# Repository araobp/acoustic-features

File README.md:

# Acoustic features for low-end edge AI

**=> [Acoustic feature gallery (2D images)](./GALLERY.md)**

## Demo video on YouTube

Acoustic features acquired by my Acoustic Feature Camera:
- [video](https://youtu.be/UvSJ3fOOCXc)

Inference using X-CUBE-AI on STM32L476RG:
- [video](https://www.youtube.com/watch?v=wbkjt2Bl5TY)

Inference using Keras/TensorFlow on PC instead of X-CUBE-AI on STM32L476RG:
- [video 1](https://youtu.be/RV7oED41P2w)
- [video 2](https://youtu.be/4BaBL-gmQBk)

## Review on this project

I have discoverd that **low-end edge AI works very well** as long as the conditions described in this README are satisfied. If simple classification is a requirment, think of low-cost AI based on MCU before MPU/FPGA/GPU!

 I find the "life log" use case (dataset: "my home") in this project works very well, but the problem is that it takes a lot of efforts -- three hours for acquiring dataset at each room in my house. This is my hobboy project, and I do not need to worry about if this can make a profit or not.
 
"key word detection" use case is also not so bad. It can be used as voice commands to controll home applicances, such as "turn on!" or "turn off!".

"acoustic scene classification" is the hardest due to the disturbance from surrounding noises. I think it is not useful in a real world.

## Use cases in this project

- life log
- always-on key word detection (e.g., "OK Google" or "Alexa!")
- musical instrument classification
- acoustic scene classification

I have tested all of the use cases above, and confirmed that my device works well.

**Note: the size of neural network is so small that it is not a general purpose tool -- it is good at very limited number of classes.**

## Architecture

```
                                                         ARM Cortex-M4(STM32L476RG)
                                         ***** pre-processing *****           ***** inference *****
                                      ................................................................
                                      :   Filters for feature extraction        Inference on CNN     :
                                      :                                         ..................   :
Sound/voice ))) [MEMS mic]--PDM-->[DFSDM]--+->[]->[]->[]->[]---+----Features--->: code generated :   :
                                      :    |                   |                : by X-CUBE-AI   :   :
                                      :    +------------+      |                ..................   :
                                      :     +-----------|------+                                     :
                                      :     |           |                                            :
                                      :     V           V                                            :
                                      :..[USART]......[DAC]..........................................:
                                            |           |
                                            |           | *** monitoring raw sound ***
                                            |           +---> [Analog filter] --> head phone
                                       (features)
                                            |
                                            | *** learning ***
                                            +--(dataset)--> [oscilloscope.py/Win10 or RasPi3] Keras/TensorFlow
                                            |
                                            | *** inference ***
                                            +--(dataset)--> [oscilloscope.py/Win10 or RasPi3] Keras/TensorFlow
```

Platform:
- [Platform and tool chain](./PLATFORM.md)

## System components

I developed the following components:

- ["Acoustic feature camera" for deep learning (CubeMX/TrueSTUDIO)](./stm32/acoustic_feature_camera)
- [Arduino shield of one MEMS microphone with BLE module (KiCAD)](./kicad)
- [Oscilloscope GUI implementation on matplotlib/Tkinter (Python)](./oscilloscope)
- [Logger GUI (HTML5)](./html5)

## Deep learning on Keras/TensorFlow

I acquired data on my own by using the components above, and it took a lot of time and effort.

- [Dataset of each use case](./dataset)
- [Executing deep learning on Jupyter Notebook](./keras)
- [Dataset format](./FORMAT.md)

### Modeling a neural network

To run a neural network on MCU (STM32 in this project), it is necessary to make the network small enough to fit it into the RAM and the flash memory:
- Adopt a CNN model that is relatively smaller than other network models.
- Perform pre-processing based on signal processing to extract features for CNN.

Usually, raw sound data (PCM) is transformed into the following "coefficients" as features:
- MFSCs (Mel Frequency Spectral Coefficients): the technique is to mimic the human auditory system.
- MFCCs (Mel Frequency Cepstral Coefficients): the technique is similar to JPEG/MPEG's data compression.

**My experiments so far showed that MFSCs+CNN ourperformed MFCCs+DNN or MFCCs+CNN.** And DNN tends to use more memory space than CNN does (more flash memory space, in case of X-CUBE-AI). So I use MFSCs for deep learning in this project.

### CNN size

The following CNN model performs very well and avoids over-fittting in most of the use cases I have ever tried:

```
Orignal data size: PCM 16bit 512*32 (26.3msec*32)

SFFT/Spectrogram size
- Stride: 13.2msec * 64
- Ovelap: 50%

MFSCs resolution: filterbank of 40 triagle filters
Quantized input tensor: MFSCs int8_t (64, 40, 1)

However, X-CUBE-AI currently supports float32_t only, so int8_t is just for transmitting the data to PC over UART.

CNN model on Keras
_________________________________________________________________
Layer (type)                 Output Shape              Param #   
=================================================================
conv2d_81 (Conv2D)           (None, 62, 38, 8)         80        
_________________________________________________________________
max_pooling2d_79 (MaxPooling (None, 31, 19, 8)         0         
_________________________________________________________________
dropout_57 (Dropout)         (None, 31, 19, 8)         0         
_________________________________________________________________
conv2d_82 (Conv2D)           (None, 29, 17, 16)        1168      
_________________________________________________________________
max_pooling2d_80 (MaxPooling (None, 14, 8, 16)         0         
_________________________________________________________________
dropout_58 (Dropout)         (None, 14, 8, 16)         0         
_________________________________________________________________
conv2d_83 (Conv2D)           (None, 12, 6, 32)         4640      
_________________________________________________________________
max_pooling2d_81 (MaxPooling (None, 6, 3, 32)          0         
_________________________________________________________________
dropout_59 (Dropout)         (None, 6, 3, 32)          0         
_________________________________________________________________
flatten_27 (Flatten)         (None, 576)               0         
_________________________________________________________________
dense_62 (Dense)             (None, 128)               73856     
_________________________________________________________________
dropout_60 (Dropout)         (None, 128)               0         
_________________________________________________________________
dense_63 (Dense)             (None, 18)                2322      
=================================================================
Total params: 82,066
Trainable params: 82,066
Non-trainable params: 0
```

### Visualization of convolution layers

**=> [Japanese word "sushi" via convolution layer](./keras/Visualization_sushi.ipynb)**

### Memory consumption and inference performance

I loaded a trained CNN model (Keras model) into Cube.AI and generated code for inference. The model consumed only 25KBytes of SRAM and 105Kbytes (compressed) of Flash memory, and the duration of inference was around 170msec on STM32L476RG.

The duration of 170msec is acceptible (not too slow) in my use cases.

And I know that Arm is working on [Helium](https://www.arm.com/why-arm/technologies/helium), so it will be able to process acoustic features for inference in real time.

## Noise problems

```
         Room impulse response
                   :
                   V
Sound -->(Line distortion)--(+)->[Feature engineering]--Feature->[Normalization]->[Neural Network]->Inference
              convolved      ^
                             | Added
                             |
                      (Ambient noise)
```

### Effect of room impulse response on inference

I have been observing that **room impulse response** (it turns into **line distortion**) has an lot of effect on inference.

My strategy for tackling the problem is:
- use **the same device** for both acquiring features and inference on the device.
- use the device **at the same location** for both acquiring features and inference.
- never change the values of parameters for feature engineering (e.g., parameters for filters).

If the above conditions are satisfied, this small neural network works very well.

### Effect of ambient noise on inference

I have been observing that sound of air conditioner affects accuracy of inference significantly.

## References

- ["New Architectures Bringing AI to the Edge"](https://www.eetimes.com/document.asp?doc_id=1333920).
- [VGGish](https://github.com/tensorflow/models/tree/master/research/audioset)
- [Speech Processing for Machine Learning: Filter banks, Mel-Frequency Cepstral Coefficients (MFCCs) and What's In-Between](https://haythamfayek.com/2016/04/21/speech-processing-for-machine-learning.html)
- [STM32 Cube.AI](https://www.st.com/content/st_com/en/stm32-ann.html)

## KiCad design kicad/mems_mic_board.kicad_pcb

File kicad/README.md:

# Arduino shield of one MEMS microphone with RN4020

## Arduino shield

==> **[Schematic](./mems_mic_board.pdf)**

Note: the yellow jumper cable is for the MEMS mic to receive clock signal from DFSDM.

## Wireless transport

I follow the output from my [iot-wireless](https://github.com/araobp/iot-wireless) project.

The following is a screen shot of BLE Scanner on Android:

## Parts

- [Knowles SPM0405HD4H MEMS microphones](http://akizukidenshi.com/catalog/g/gM-05577/)
- [Universal board](http://akizukidenshi.com/catalog/g/gP-07555/)
- [Microchip RN4020 BLE module](http://akizukidenshi.com/catalog/g/gK-11102/)

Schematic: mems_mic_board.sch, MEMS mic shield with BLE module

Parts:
J1, J5: Conn_01x08_Male; Pin Header 8P
J2: Conn_01x06_Male; Pin Header 6P
J3: Conn_01x01_Male; Pin_header_1P
J4: Conn_01x10_Male; Pin Header 10P
J6: Conn_01x06_Female; Pin_Socket_6P
U1: tactile_sw; tactile_sw_4p
U3: mems_mic; MEMS_mic

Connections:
+3V3: J1.4, U3.8 (VDD)
GND: J1.6, J6.6, U1.2, U3.1 (GND), U3.2 (L/R)
unnamed: J1.3, U1.4
unnamed: J3.1, U3.4 (CLK)
unnamed: J4.9, U3.5 (DAT)
unnamed: J4.10, J6.3
unnamed: J5.6, J6.2
U5V: J1.5, J6.4

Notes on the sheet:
PC7 (DFSDM_DATAIN2)
Vin
GND
3.3V
RESET
PC2 (DFSDM_CKOUT)
Mic L
PA9 (USART1 TX)
PA10 (USART1 RX)
RN4020 module

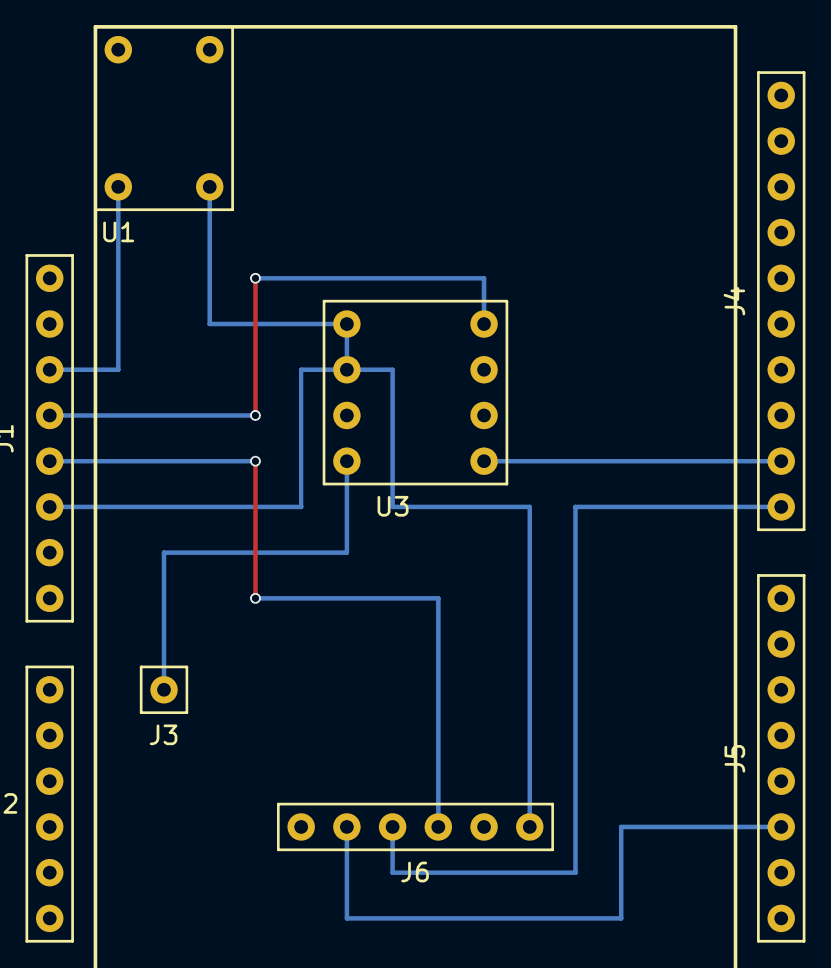
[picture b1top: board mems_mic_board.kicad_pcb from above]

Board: 2 copper layers, 8 parts (0 on the bottom side), 8 nets.

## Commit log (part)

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2018-12-16 object oriented way
2018-12-17 Weakning pre-emphasis for Endfire beam forming to compensate attenuation
2018-12-19 Integrate paramters into dataset.yaml
2018-12-21 bug fix
2018-12-21 Rename SHUTTER with FEATURES
2018-12-22 Avoid overflow of MFCCs
2018-12-24 8bit quantization
2018-12-24 add remove DC option for mel spectrogram
2018-12-26 Increase NUM_FILTERS from 40 to 64
2019-01-09 Migrate to my DCT Type-II implementation
2019-02-09 update pattern
2019-02-09 MFSCs of music instruments
2019-02-09 AI inference performane test
2019-02-09 screen shot of x-cube-ai
2019-02-09 Integration with X-CUBE-AI
2019-02-09 Integrated code
2019-02-10 successful integration with AI
2019-02-11 LCD output
2019-02-28 Rename
2019-03-02 key word detection experiment successful
2019-03-02 updatet
2019-03-23 support data serializatin with pickle
2019-03-24 bug fix: I forgot to add standard normalzation
2019-03-30 life logger
2019-04-29 support BLE
2019-04-29 Remove beam forming
2019-04-29 remove pics
2019-04-30 update report
2019-04-30 remove beam forming feature
2019-04-30 main.html
2019-04-30 README update
2019-05-07 move html5 folder to https://github.com/araobp/iot-wireless
2019-05-11 Bug fix for #32
